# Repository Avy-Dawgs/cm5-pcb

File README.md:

# cm5-pcb
Design files for board to host Raspberry PI Compute Module 5.

### Source of Starting Project
https://pip.raspberrypi.com/categories/1098-design-files

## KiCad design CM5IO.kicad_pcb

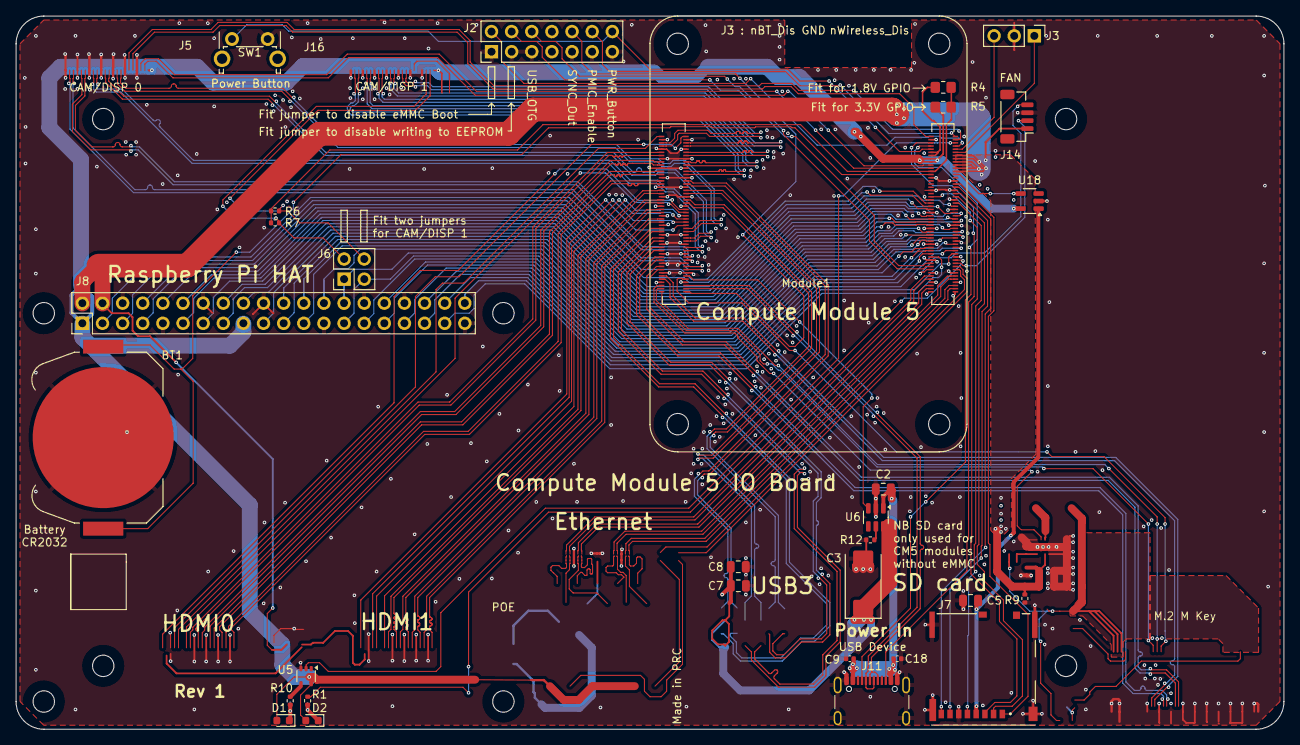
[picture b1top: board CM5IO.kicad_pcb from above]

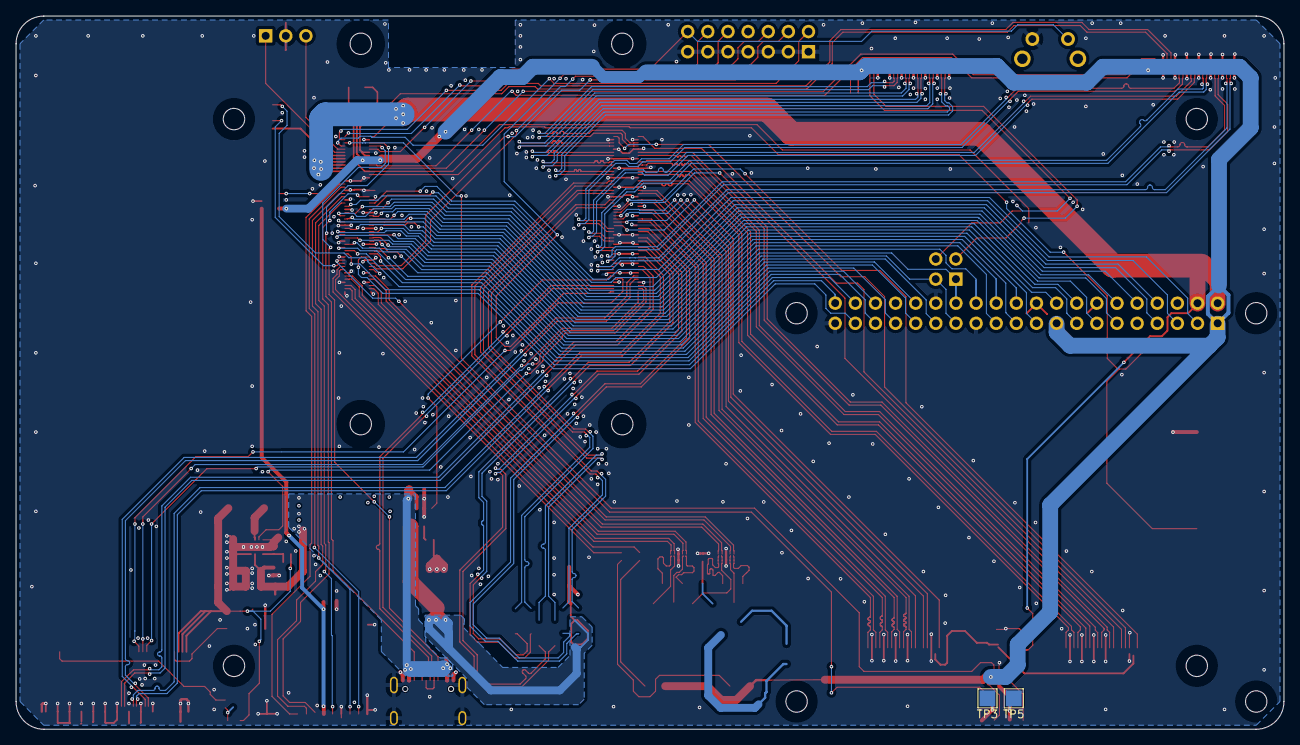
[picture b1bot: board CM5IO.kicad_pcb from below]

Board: 4 copper layers, 160.0 x 90.0 mm, 40 parts (2 on the bottom side), 67 nets.

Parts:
BT1: Battery_Cell; BatteryHolder_Keystone_3034_1x20mm
C2, C5, C7, C8: 10u; C_0805_2012Metric
C3: 100uF; CP_EIA-7343-31_Kemet-D
C9, C18: 100n; C_0402_1005Metric
D1: LED Red; LED_0603_1608Metric
D2: LED Green; LED_0603_1608Metric
H1, H2, H3, H4, H5, H6, H7, H8: MountingHole; MountingHole_2.7mm_M2.5_DIN965
J2: Conn_02x07_Odd_Even; PinHeader_2x07_P2.54mm_Vertical
J3: Conn_01x03; PinHeader_1x03_P2.54mm_Vertical
J6: THD-02-R; PinHeader_2x02_P2.54mm_Vertical
J7: Micro_SD_Card_Det; SDCARD_MOLEX_503398-1892
J8: THD-20-R; PinHeader_2x20_P2.54mm_Vertical
J11: USB_C_Receptacle_USB2.0; USB_C_Receptacle_GCT_USB4105-xx-A_16P_TopMnt_Horizontal
J14: JST_SHBM04B-SRSS-TB; JST_SH_BM04B-SRSS-TB_1x04-1MP_P1.00mm_Vertical
Module1: ComputeModule5-CM5; Raspberry-Pi-5-Compute-Module
R1, R10: 1k; R_0402_1005Metric
R4: nf; R_0805_2012Metric_Pad1.20x1.40mm_HandSolder
R5: 0R; R_0805_2012Metric_Pad1.20x1.40mm_HandSolder
R6, R7, R9: 2.2K 1%; R_0402_1005Metric
R12: 15K 1%; R_0402_1005Metric
SW1: Right angle Tact button; SW_Tactile_SPST_Angled_PTS645Vx58-2LFS
TP3, TP5: TestPoint; TestPoint_Pad_2.0x2.0mm
U5: 74LVC1G07SE-7; SOT-353_SC-70-5
U6: AP22653W6; SOT-23-6
U18: RT9742GGJ5; SOT-23-5

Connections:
/+3.3v: D1.2 (A), D2.2 (A), J8.1, J8.17, Module1.84 (+3.3v_(Output)), Module1.86 (+3.3v_(Output)), R5.1, U5.5 (VCC), U18.5 (IN)
/+5v: C9.1, C18.1, J8.2, J8.4, J11.A4 (VBUS), J11.A9 (VBUS), J11.B4 (VBUS), J11.B9 (VBUS), J14.1, Module1.77 (+5v_(Input)), Module1.79 (+5v_(Input)), Module1.81 (+5v_(Input)), Module1.83 (+5v_(Input)), Module1.85 (+5v_(Input)), Module1.87 (+5v_(Input)), R9.1
/CC1: J11.A5 (CC1), Module1.94 (CC1)
/CC2: J11.B5 (CC2), Module1.96 (CC2)
/CM5_GPIO (GPIO, SDCARD)/+1.8v: Module1.88 (+1.8v_(Output)), Module1.90 (+1.8v_(Output)), R4.1
/CM5_GPIO (GPIO, SDCARD)/BT_nDis: J3.3, Module1.91 (BT_nDisable)
/CM5_GPIO (GPIO, SDCARD)/EEPROM_nWP: J2.4, Module1.20 (EEPROM_nWP)
/CM5_GPIO (GPIO, SDCARD)/GPIO2: J8.3, Module1.58 (GPIO2)
/CM5_GPIO (GPIO, SDCARD)/GPIO3: J8.5, Module1.56 (GPIO3)
/CM5_GPIO (GPIO, SDCARD)/GPIO4: J8.7, Module1.54 (GPIO4)
/CM5_GPIO (GPIO, SDCARD)/GPIO5: J8.29, Module1.34 (GPIO5)
/CM5_GPIO (GPIO, SDCARD)/GPIO6: J8.31, Module1.30 (GPIO6)
/CM5_GPIO (GPIO, SDCARD)/GPIO7: J8.26, Module1.37 (GPIO7)
/CM5_GPIO (GPIO, SDCARD)/GPIO8: J8.24, Module1.39 (GPIO8)
/CM5_GPIO (GPIO, SDCARD)/GPIO9: J8.21, Module1.40 (GPIO9)
/CM5_GPIO (GPIO, SDCARD)/GPIO10: J8.19, Module1.44 (GPIO10)
/CM5_GPIO (GPIO, SDCARD)/GPIO11: J8.23, Module1.38 (GPIO11)
/CM5_GPIO (GPIO, SDCARD)/GPIO12: J8.32, Module1.31 (GPIO12)
/CM5_GPIO (GPIO, SDCARD)/GPIO13: J8.33, Module1.28 (GPIO13)
/CM5_GPIO (GPIO, SDCARD)/GPIO14: J8.8, Module1.55 (GPIO14)
/CM5_GPIO (GPIO, SDCARD)/GPIO15: J8.10, Module1.51 (GPIO15)
/CM5_GPIO (GPIO, SDCARD)/GPIO16: J8.36, Module1.29 (GPIO16)
/CM5_GPIO (GPIO, SDCARD)/GPIO17: J8.11, Module1.50 (GPIO17)
/CM5_GPIO (GPIO, SDCARD)/GPIO18: J8.12, Module1.49 (GPIO18)
/CM5_GPIO (GPIO, SDCARD)/GPIO19: J8.35, Module1.26 (GPIO19)
/CM5_GPIO (GPIO, SDCARD)/GPIO20: J8.38, Module1.27 (GPIO20)
/CM5_GPIO (GPIO, SDCARD)/GPIO21: J8.40, Module1.25 (GPIO21)
/CM5_GPIO (GPIO, SDCARD)/GPIO22: J8.15, Module1.46 (GPIO22)
/CM5_GPIO (GPIO, SDCARD)/GPIO23: J8.16, Module1.47 (GPIO23)
/CM5_GPIO (GPIO, SDCARD)/GPIO24: J8.18, Module1.45 (GPIO24)
/CM5_GPIO (GPIO, SDCARD)/GPIO25: J8.22, Module1.41 (GPIO25)
/CM5_GPIO (GPIO, SDCARD)/GPIO26: J8.37, Module1.24 (GPIO26)
/CM5_GPIO (GPIO, SDCARD)/GPIO27: J8.13, Module1.48 (GPIO27)
/CM5_GPIO (GPIO, SDCARD)/GPIO_VREF: Module1.78 (GPIO_VREF(1.8v/3.3v_Input)), R4.2, R5.2, R6.1, R7.1
/CM5_GPIO (GPIO, SDCARD)/ID_SC: J6.1, J8.28, Module1.35 (ID_SC)
/CM5_GPIO (GPIO, SDCARD)/ID_SD: J6.3, J8.27, Module1.36 (ID_SD)
/CM5_GPIO (GPIO, SDCARD)/PMIC_ENABLE: J2.12, Module1.99 (PMIC_ENABLE)
/CM5_GPIO (GPIO, SDCARD)/PWM: J14.2, Module1.19 (FAN_PWM)
/CM5_GPIO (GPIO, SDCARD)/PWR_BUT: J2.14, Module1.92 (PWR_BUT), SW1.1
/CM5_GPIO (GPIO, SDCARD)/SD_CLK: J7.5 (CLK), Module1.57 (SD_CLK)
/CM5_GPIO (GPIO, SDCARD)/SD_CMD: J7.3 (CMD), Module1.62 (SD_CMD)
/CM5_GPIO (GPIO, SDCARD)/SD_DAT0: J7.7 (DAT0), Module1.63 (SD_DAT0)
/CM5_GPIO (GPIO, SDCARD)/SD_DAT1: J7.8 (DAT1), Module1.67 (SD_DAT1)
/CM5_GPIO (GPIO, SDCARD)/SD_DAT2: J7.1 (DAT2), Module1.69 (SD_DAT2)
/CM5_GPIO (GPIO, SDCARD)/SD_DAT3: J7.2 (DAT3/CD), Module1.61 (SD_DAT3)
/CM5_GPIO (GPIO, SDCARD)/SD_PWR: C5.1, J7.4 (VDD), U18.1 (OUT)
/CM5_GPIO (GPIO, SDCARD)/SD_PWR_ON: Module1.75 (SD_PWR_ON), U18.4 (EN)
/CM5_GPIO (GPIO, SDCARD)/SYNC_OUT: J2.6, Module1.18 (Ethernet_SYNC_OUT(3.3v))
/CM5_GPIO (GPIO, SDCARD)/TACHO: J14.4, Module1.16 (FAN_TACHO)
/CM5_GPIO (GPIO, SDCARD)/USBOTG: J2.10, Module1.101 (USB_OTG_ID)
/CM5_GPIO (GPIO, SDCARD)/VBAT: BT1.1 (+), Module1.76 (VBAT)
/CM5_GPIO (GPIO, SDCARD)/WL_nDis: J3.1, Module1.89 (WiFi_nDisable)
/CM5_GPIO (GPIO, SDCARD)/nPWR_LED: Module1.95 (LED_nPWR), U5.2
/CM5_GPIO (GPIO, SDCARD)/nRPIBOOT: J2.2, Module1.93 (nRPIBOOT)
/CM5_HighSpeed/+5v: C2.1, U6.1 (IN)
/CM5_HighSpeed/SCL1: J6.2, R7.2
/CM5_HighSpeed/SDA1: J6.4, R6.2
/CM5_HighSpeed/VBUS: C3.1, C7.1, C8.1, U6.6 (OUT)
/CM5_HighSpeed/VBUS_EN: Module1.111 (VBUS_EN), U6.3 (EN)
/USB2_N: J11.A7 (D-), J11.B7 (D-), Module1.103 (USB2_N)
/USB2_P: J11.A6 (D+), J11.B6 (D+), Module1.105 (USB2_P)
GND: BT1.2 (-), C2.2, C3.2, C5.2, C7.2, C8.2, C9.2, C18.2, J2.1, J2.3, J2.5, J2.7, J2.9, J2.11, J2.13, J3.2, J7.6 (VSS), J7.11 (SHIELD), J8.6, J8.9, J8.14, J8.20, J8.25, J8.30, J8.34, J8.39, J11.A1 (GND), J11.A12 (GND), J11.B1 (GND), J11.B12 (GND), J11.S1 (SHIELD), J14.3, Module1.1 (GND), Module1.2 (GND), Module1.7 (GND), Module1.8 (GND), Module1.13 (GND), Module1.14 (GND), Module1.22 (GND), Module1.23 (GND), Module1.32 (GND), Module1.33 (GND), Module1.42 (GND), Module1.43 (GND), Module1.52 (GND), Module1.53 (GND), Module1.59 (GND), Module1.60 (GND), Module1.65 (GND), Module1.66 (GND), Module1.71 (GND), Module1.74 (GND), Module1.98 (GND), Module1.107 (GND), Module1.108 (GND), Module1.113 (GND), Module1.114 (GND), Module1.119 (GND), Module1.120 (GND), Module1.125 (GND), Module1.126 (GND), Module1.131 (GND), Module1.132 (GND), Module1.137 (GND), Module1.138 (GND), Module1.144 (GND), Module1.150 (GND), Module1.155 (GND), Module1.156 (GND), Module1.161 (GND), Module1.162 (GND), Module1.167 (GND), Module1.168 (GND), Module1.173 (GND), Module1.174 (GND), Module1.179 (GND), Module1.180 (GND), Module1.185 (GND), Module1.186 (GND), Module1.191 (GND), Module1.192 (GND), Module1.197 (GND), Module1.198 (GND), R9.2, R12.2, SW1.2, U5.3 (GND), U6.2 (GND), U18.2 (GND)
unnamed: D1.1 (K), R10.1, TP5.1
unnamed: D2.1 (K), R1.1, TP3.1
unnamed: Module1.21 (LED_nACT), R1.2
unnamed: R10.2, U5.4
unnamed: R12.1, U6.5 (ILIM)

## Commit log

2025-05-01 add CM5IO board as starting point
2025-05-01 update version of kicad project
2025-05-01 add link to CM5IO download to readme
2025-05-01 remove ethernet, pcie, hdmi
2025-05-03 add wbk files
